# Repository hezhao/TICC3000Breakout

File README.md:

## Summary

This is a basic breakout for the TI CC3000 WiFi module based on [Kuy's Design](https://github.com/kuym/TICC3000Breakout), the only difference is that this board uses all 0805 components. 
EAGLE sources.  Open Source / Open Hardware (CC-BY-SA-3.0). You can order the PCB From [OSH Park](http://oshpark.com/shared_projects/wW0yLq3M)

## Parts

	C1: 1pF 0805
	L1, L2: do not populate
	C2: 4.7uF 0805
	C3: 100nF 0805

You may adjust all component values to taste (only C1's value is important.)

## Notes
- Board doesn't pass OSH Park design rule, mainly issues with clearance and stop marks
- Careful with plated ground Vias when soldering components

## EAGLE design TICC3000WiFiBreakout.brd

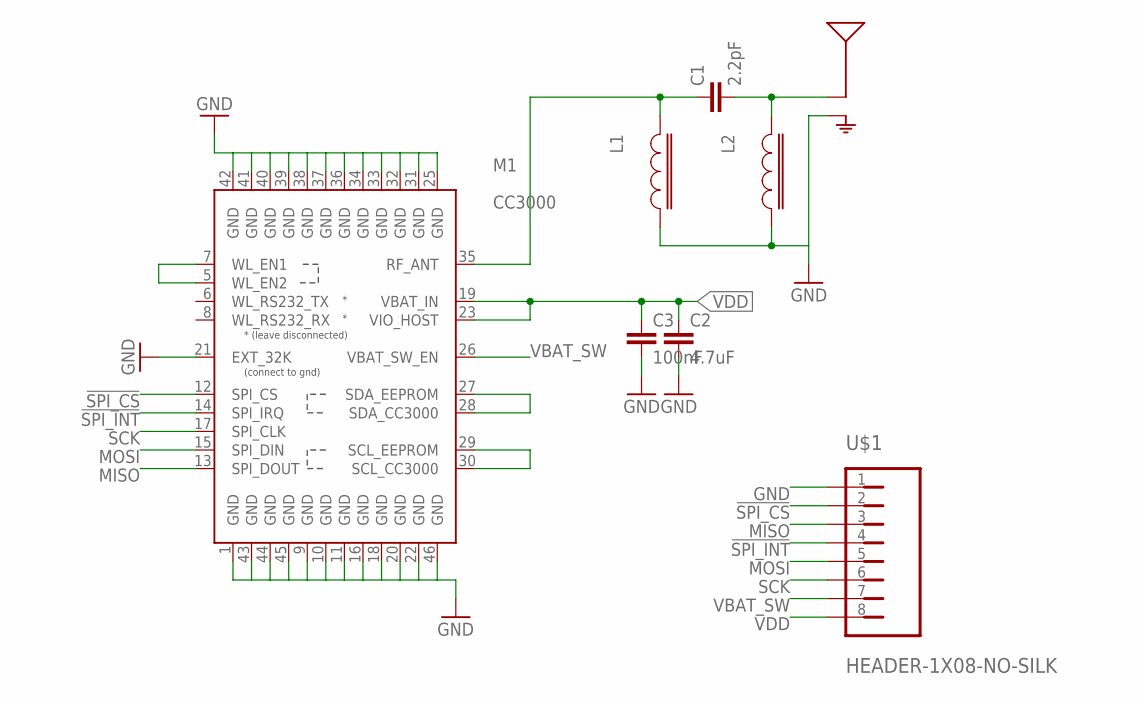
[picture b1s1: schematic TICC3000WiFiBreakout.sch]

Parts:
ANT1: ANTENNA-TRACE-WITH-GND-2.450GHZ-TI-AN043; ANTENNA-2.450GHZ-TI-AN043
C1: 2.2pF; 0805
C2: 4.7uF; 0805
C3: 100nF; 0805
L1, L2: INDUCTOR-0402-MIN; 0402-MIN
M1: CC3000; TI-CC3000-WIFI-MODULE
U$1: HEADER-1X08-NO-SILK

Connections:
!SPI_CS: M1.12 (SPI_CS), U$1.2
!SPI_INT: M1.14 (SPI_IRQ), U$1.4
GND: ANT1.RFGND (GND), C2.1, C3.1, L1.2, L2.2, M1.1 (GND), M1.9 (GND), M1.10 (GND), M1.11 (GND), M1.16 (GND), M1.18 (GND), M1.20 (GND), M1.21 (EXT_32K), M1.22 (GND), M1.25 (GND), M1.31 (GND), M1.32 (GND), M1.33 (GND), M1.34 (GND), M1.36 (GND), M1.37 (GND), M1.38 (GND), M1.39 (GND), M1.40 (GND), M1.41 (GND), M1.42 (GND), M1.43 (GND), M1.44 (GND), M1.45 (GND), M1.46 (GND), U$1.1
MISO: M1.13 (SPI_DOUT), U$1.3
MOSI: M1.15 (SPI_DIN), U$1.5
unnamed: M1.27 (SDA_EEPROM), M1.28 (SDA_CC3000)
unnamed: M1.29 (SCL_EEPROM), M1.30 (SCL_CC3000)
unnamed: M1.5 (WL_EN2), M1.7 (WL_EN1)
unnamed: C1.2, L1.1, M1.35 (RF_ANT)
unnamed: ANT1.ANT (RF), C1.1, L2.1
SCK: M1.17 (SPI_CLK), U$1.6
VBAT_SW: M1.26 (VBAT_SW_EN), U$1.7
VDD: C2.2, C3.2, M1.19 (VBAT_IN), M1.23 (VIO_HOST), U$1.8

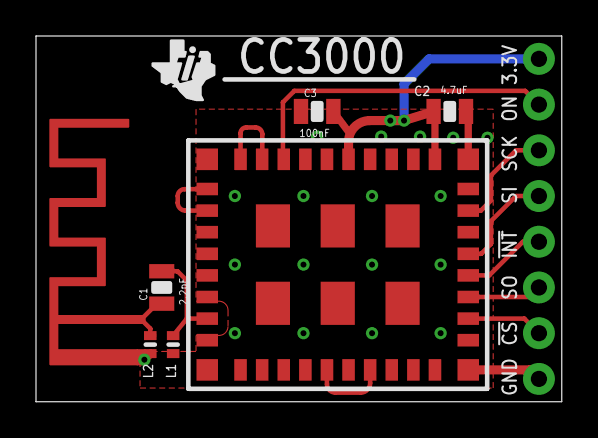
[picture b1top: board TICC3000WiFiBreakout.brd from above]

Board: 2 copper layers, 29.2 x 20.3 mm, 8 parts (0 on the bottom side), 13 nets.

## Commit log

2014-02-12 submitted to OSH Park
2014-02-26 added assembled board pic, added stencil dxf, added silhouette studio project file
2014-02-26 change pic url
